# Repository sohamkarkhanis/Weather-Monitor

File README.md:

# Weather Monitor

Weather Monitor is an ESP32-based project featuring:

- Real-time data capture without the need for an RTC (Real-Time Clock), achieved through NTP (Network Time Protocol) synchronization.
- Seamless integration with the ThingSpeak IoT platform.
- The hosting of a web server directly on the ESP32.

## Project Overview

- Utilizes two sensors: BMP280 for atmospheric pressure and altitude, and DHT11 for temperature and humidity measurements.
- Fetches accurate time and date data from the `pool.ntp.org` server, eliminating the need for an RTC module by connecting to a WiFi router in Station mode.
- Hosts a web server on the ESP32, allowing users to access and download captured data as a `.csv` file when connected to it as a SoftAP.
- Regularly sends sampled data to the ThingSpeak platform for real-time monitoring and analysis.
- Displays instantaneous readings on an OLED display.
- PCB layout, schematics, and Gerber files are provided for your convenience!

## License

This project is open-source and licensed under the [MIT License](LICENSE). Feel free to contribute, modify, or use it for educational purposes :)

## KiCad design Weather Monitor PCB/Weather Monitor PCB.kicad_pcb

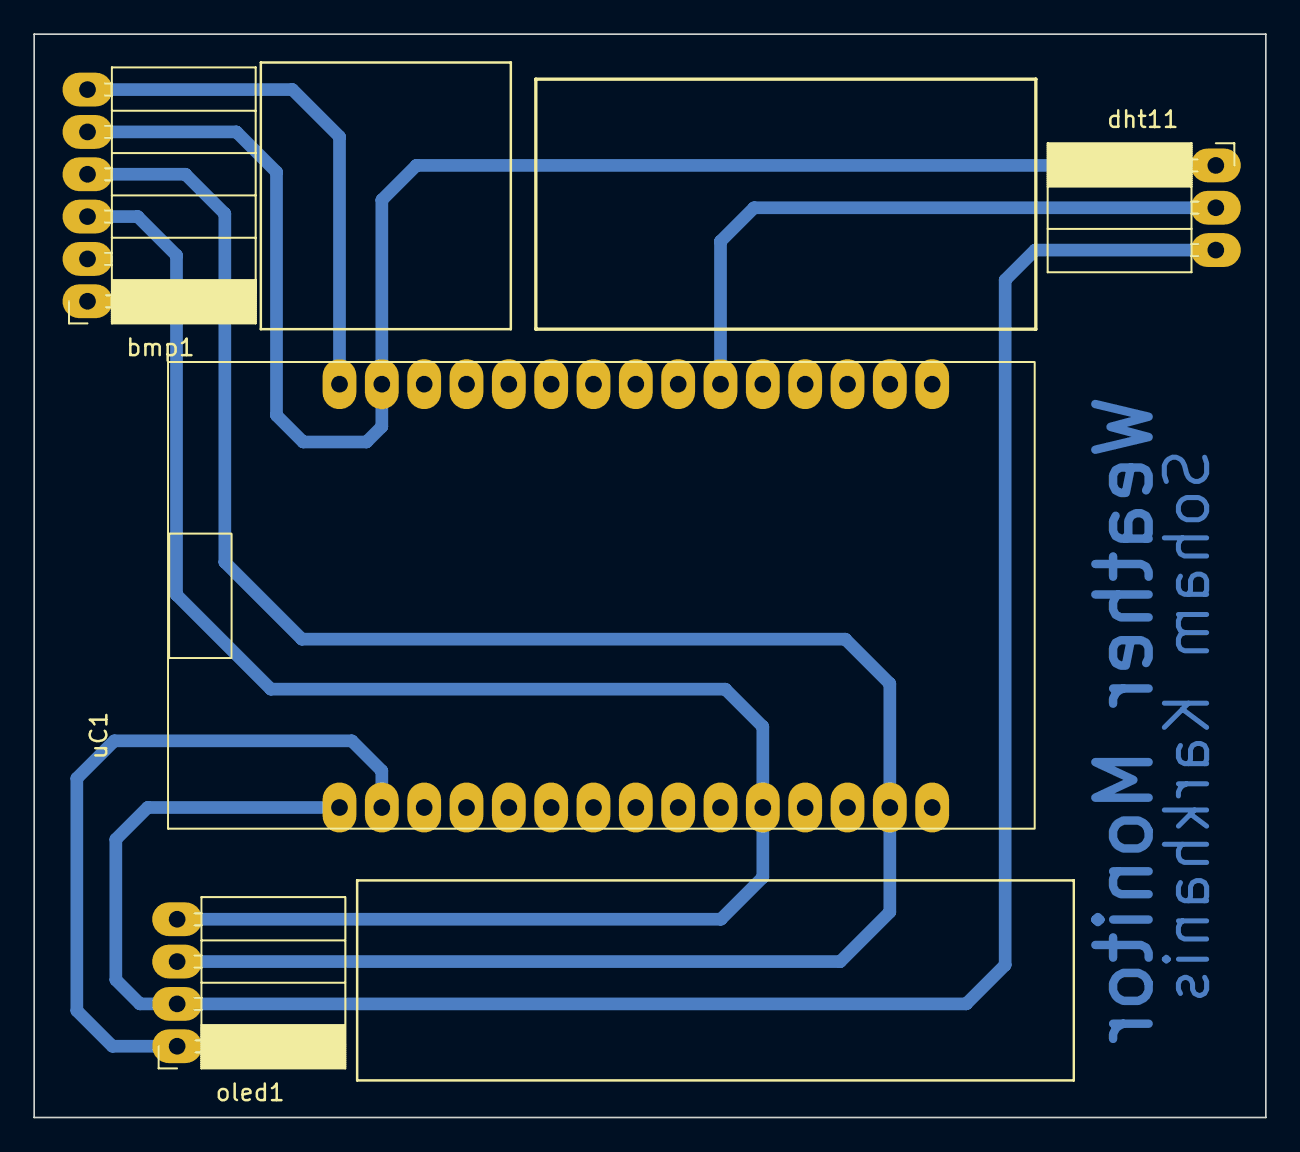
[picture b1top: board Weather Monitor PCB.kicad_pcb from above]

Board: 2 copper layers, 73.9 x 65.0 mm, 4 parts (0 on the bottom side), 6 nets.

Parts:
bmp1: Conn_01x06_Pin; PinSocket_1x06_P2.54mm_Horizontal
dht11: Conn_01x03_Pin; PinSocket_1x03_P2.54mm_Horizontal
oled1: Conn_01x04_Male; PinSocket_1x04_P2.54mm_Horizontal
uC1: ESP32_30_Pin

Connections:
/3V3: dht11.3, oled1.2, uC1.1 (3V3)
/5V: bmp1.6, uC1.30 (VIN)
/DHT11: dht11.2, uC1.21 (GPIO32)
/GND: bmp1.5, dht11.1, oled1.1, uC1.2 (GND), uC1.29 (GND)
/SCL: bmp1.4, oled1.3, uC1.14 (I2C SCL)
/SDA: bmp1.3, oled1.4, uC1.11 (I2C SDA)

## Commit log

2023-10-04 Init
2023-10-12 +ifdef INIT_CSV
    added functionality to control whether to overwrite the existing data in the WeatherData.csv on boot each time, or continue appending to the previous set of readings
